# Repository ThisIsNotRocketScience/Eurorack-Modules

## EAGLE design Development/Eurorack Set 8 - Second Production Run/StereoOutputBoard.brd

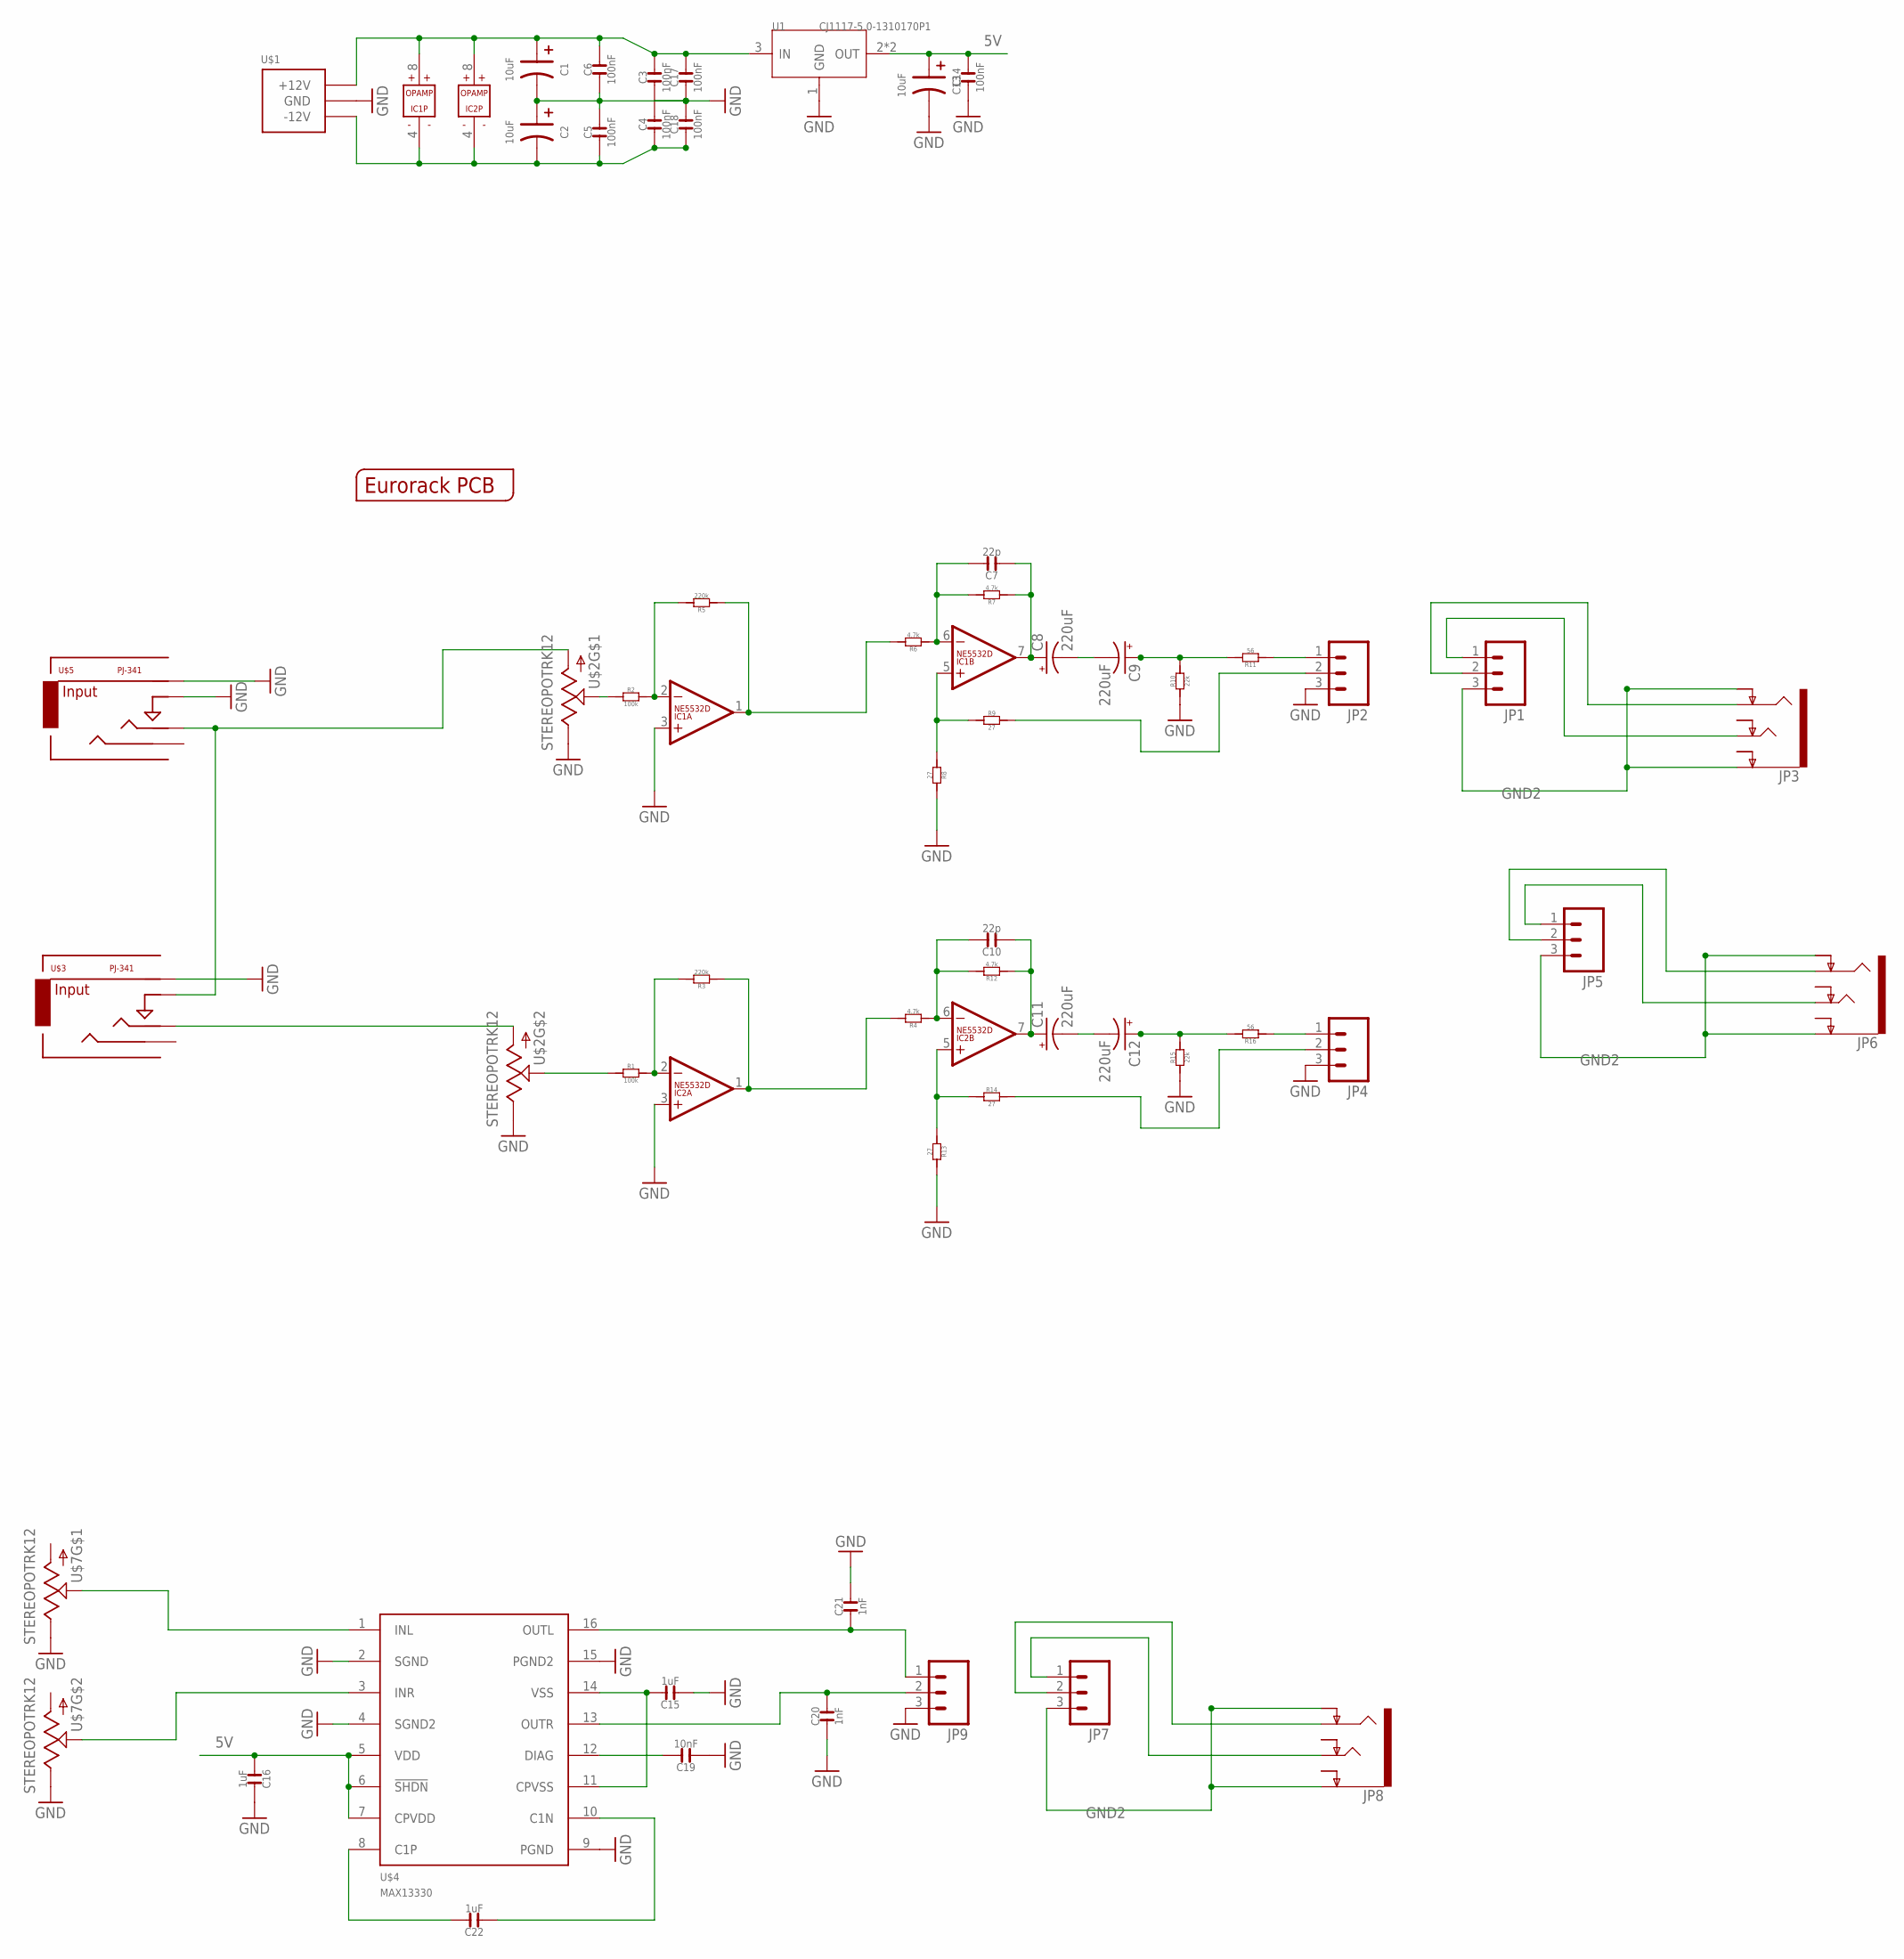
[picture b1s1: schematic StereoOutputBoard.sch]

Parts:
C1, C2, C13: 10uF; AVX-A
C3, C4, C5, C6, C14, C17, C18: 100nF; C0603
C7, C10: 22p; C0603
C8, C9, C11, C12: 220uF; 153CLV-0505
C15, C16, C22: 1uF; C0603
C19: 10nF; C0603
C20, C21: 1nF; C0603
IC1, IC2: NE5532D; SO08
JP1, JP2, JP4, JP5, JP7, JP9: M03PTH; 1X03
JP3, JP6, JP8: AUDIO-JACK4-.25-HORIZ-TRS; AUDIO-JACK-.25-INCH-HORIZ-PTH
R1, R2: 100k; R0603
R3, R5: 220k; R0603
R4, R6, R7, R12: 4.7k; R0603
R8, R9, R13, R14: 27; R0603
R10, R15: 22k; R0603
R11, R16: 56; R0603
U1: CJ1117-5.0-1310170P1; SOT223
U$1: POWER_SIMPLE; 2X05_SMT_HEADER
U$2, U$7: STEREOPOTRK12; RK12
U$3, U$5: PJ-341; 3.5MM-JACK-SWITCH-13MM-INPUT
U$4: MAX13330; QSOP16
U$6: EURORACK_PCB4HP; EURORACK4HPPCB

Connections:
5V: C13.+ (1), C14.2, C16.1, U1.2 (OUT), U1.TER (OUT), U$4.5 (VDD), U$4.6 (!SHDN), U$4.7 (CPVDD)
+12V: C1.+ (1), C3.2, C6.2, C17.2, IC1.8 (V+), IC2.8 (V+), U1.3 (IN), U$1.9 (+12V), U$1.10 (+12V)
-12V: C2.- (2), C4.1, C5.1, C18.1, IC1.4 (V-), IC2.4 (V-), U$1.1 (-12V), U$1.2 (-12V)
GND: C1.- (2), C2.+ (1), C3.1, C4.2, C5.2, C6.1, C13.- (2), C14.1, C15.1, C16.2, C17.1, C18.2, C19.1, C20.1, C21.2, IC1.3 (+IN), IC2.3 (+IN), JP2.3, JP4.3, JP9.3, R8.2, R10.1, R13.2, R15.1, U1.1 (GND), U$1.3 (GND), U$1.4 (GND), U$1.5 (GND), U$1.6 (GND), U$1.7 (GND), U$1.8 (GND), U$2.R1_1 (E), U$2.R2_1 (E), U$3.RING@3 (RING), U$4.2 (SGND), U$4.4 (SGND2), U$4.9 (PGND), U$4.15 (PGND2), U$5.RING@3 (RING), U$5.SWITCH@3 (SWITCH), U$7.R1_1 (E), U$7.R2_1 (E)
GND2: JP1.3, JP3.P$2 (EARTH), JP3.P$5 (RING-NORM), JP5.3, JP6.P$2 (EARTH), JP6.P$5 (RING-NORM), JP7.3, JP8.P$2 (EARTH), JP8.P$5 (RING-NORM)
unnamed: JP2.1, R11.1
unnamed: JP1.1, JP3.P$6 (TIP)
unnamed: C9.+, R10.2, R11.2
unnamed: C7.1, C8.+, IC1.7 (OUT), R7.1
unnamed: IC1.5 (+IN), R8.1, R9.1
unnamed: JP2.2, R9.2
unnamed: C7.2, IC1.6 (-IN), R6.1, R7.2
unnamed: IC1.2 (-IN), R2.2, R5.2
unnamed: JP4.1, R16.1
unnamed: C12.+, R15.2, R16.2
unnamed: C10.1, C11.+, IC2.7 (OUT), R12.1
unnamed: IC1.1 (OUT), R5.1, R6.2
unnamed: C8.-, C9.-
unnamed: R2.1, U$2.R1_2 (S)
unnamed: IC2.5 (+IN), R13.1, R14.1
unnamed: JP4.2, R14.2
unnamed: C10.2, IC2.6 (-IN), R4.1, R12.2
unnamed: JP1.2, JP3.P$4 (RING)
unnamed: IC2.2 (-IN), R1.2, R3.2
unnamed: R1.1, U$2.R2_2 (S)
unnamed: IC2.1 (OUT), R3.1, R4.2
unnamed: C11.-, C12.-
unnamed: U$2.R1_3 (A), U$3.SWITCH@3 (SWITCH), U$5.TIP@3 (TIP)
unnamed: U$2.R2_3 (A), U$3.TIP@3 (TIP)
unnamed: JP5.1, JP6.P$6 (TIP)
unnamed: JP5.2, JP6.P$4 (RING)
unnamed: JP7.1, JP8.P$6 (TIP)
unnamed: JP7.2, JP8.P$4 (RING)
unnamed: C15.2, U$4.11 (CPVSS), U$4.14 (VSS)
unnamed: C19.2, U$4.12 (DIAG)
unnamed: C21.1, JP9.1, U$4.16 (OUTL)
unnamed: C20.2, JP9.2, U$4.13 (OUTR)
unnamed: C22.2, U$4.8 (C1P)
unnamed: C22.1, U$4.10 (C1N)
unnamed: U$4.1 (INL), U$7.R1_2 (S)
unnamed: U$4.3 (INR), U$7.R2_2 (S)

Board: 2 copper layers, 57 parts (1 on the bottom side), 41 nets, no tracks yet.

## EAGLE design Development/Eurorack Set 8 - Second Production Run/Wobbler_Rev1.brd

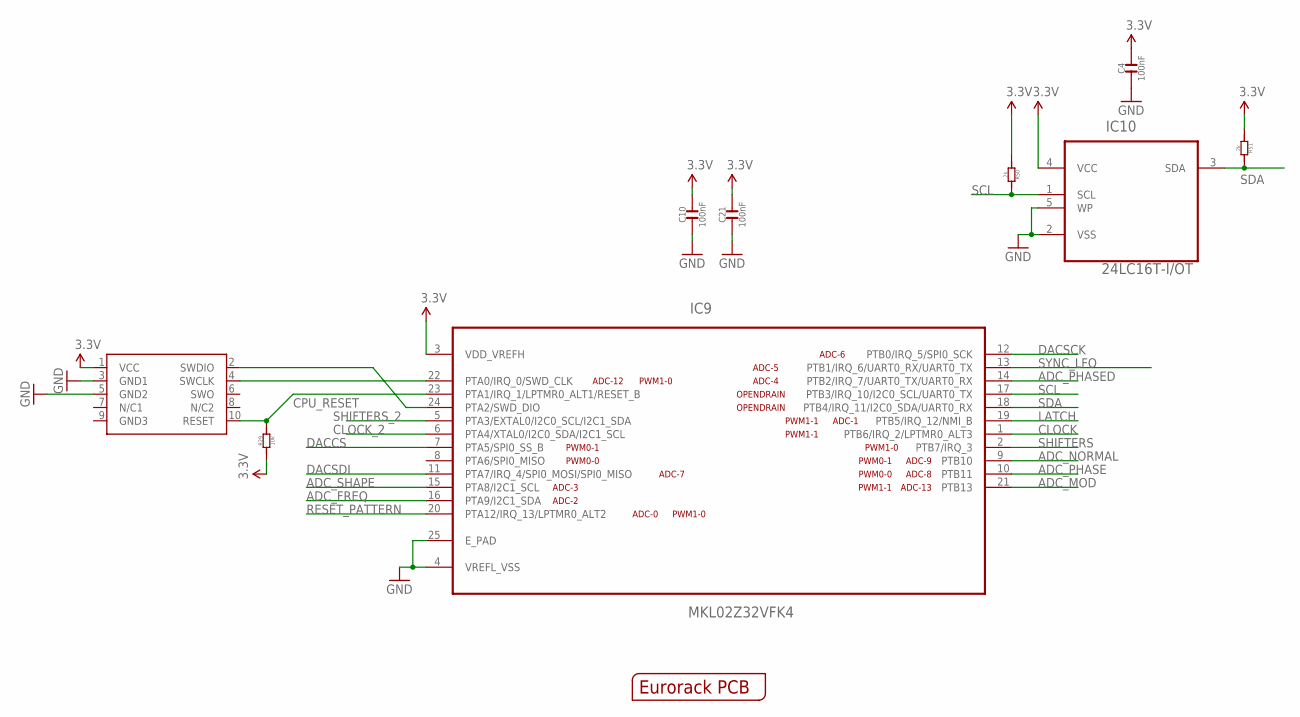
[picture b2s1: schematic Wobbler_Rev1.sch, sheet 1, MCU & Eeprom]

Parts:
C4, C10, C21: 100nF; C0603; MPN MC0603F104Z160CT
IC9: MKL02Z32VFK4; QFN50P400X400X100-25N
IC10: 24LC16T-I/OT; SOT95P290X145-5N; MPN 24LC00T-I/OT
OUTLINE: EURORACK_PCB12HP; EURORACK12HPPCB
R29: 10k; R0603
R50, R51: 2k; R0603
SWD1: CORTEX_SWD; M50-3600542

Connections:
3.3V: C4.2, C10.2, C21.2, IC9.3 (VDD_VREFH), IC10.4 (VCC), R29.1, R50.1, R51.1, SWD1.1 (VCC); also elsewhere on the board
ADC_FREQ: IC9.16 (PTA9/I2C1_SDA); also elsewhere on the board
ADC_MOD: IC9.21 (PTB13); also elsewhere on the board
ADC_NORMAL: IC9.9 (PTB10); also elsewhere on the board
ADC_PHASE: IC9.10 (PTB11); also elsewhere on the board
ADC_PHASED: IC9.14 (PTB2/IRQ_7/UART0_TX/UART0_RX); also elsewhere on the board
ADC_SHAPE: IC9.15 (PTA8/I2C1_SCL); also elsewhere on the board
CLOCK: IC9.1 (PTB6/IRQ_2/LPTMR0_ALT3); also elsewhere on the board
CLOCK_2: IC9.6 (PTA4/XTAL0/I2C0_SDA/I2C1_SCL); also elsewhere on the board
CPU_RESET: IC9.23 (PTA1/IRQ_1/LPTMR0_ALT1/RESET_B), R29.2, SWD1.10 (RESET)
DACCS: IC9.7 (PTA5/SPI0_SS_B); also elsewhere on the board
DACSCK: IC9.12 (PTB0/IRQ_5/SPI0_SCK); also elsewhere on the board
DACSDI: IC9.11 (PTA7/IRQ_4/SPI0_MOSI/SPI0_MISO); also elsewhere on the board
GND: C4.1, C10.1, C21.1, IC9.4 (VREFL_VSS), IC9.25 (E_PAD), IC10.2 (VSS), IC10.5 (WP), SWD1.3 (GND1), SWD1.5 (GND2); also elsewhere on the board
LATCH: IC9.19 (PTB5/IRQ_12/NMI_B); also elsewhere on the board
RESET_PATTERN: IC9.20 (PTA12/IRQ_13/LPTMR0_ALT2); also elsewhere on the board
SCL: IC9.17 (PTB3/IRQ_10/I2C0_SCL/UART0_TX), IC10.1 (SCL), R50.2
SDA: IC9.18 (PTB4/IRQ_11/I2C0_SDA/UART0_RX), IC10.3 (SDA), R51.2
SHIFTERS: IC9.2 (PTB7/IRQ_3); also elsewhere on the board
SHIFTERS_2: IC9.5 (PTA3/EXTAL0/I2C0_SCL/I2C1_SDA); also elsewhere on the board
SWD_CLK: IC9.22 (PTA0/IRQ_0/SWD_CLK), SWD1.4 (SWCLK)
SWD_DIO: IC9.24 (PTA2/SWD_DIO), SWD1.2 (SWDIO)
SYNC_LFO: IC9.13 (PTB1/IRQ_6/UART0_RX/UART0_TX); also elsewhere on the board

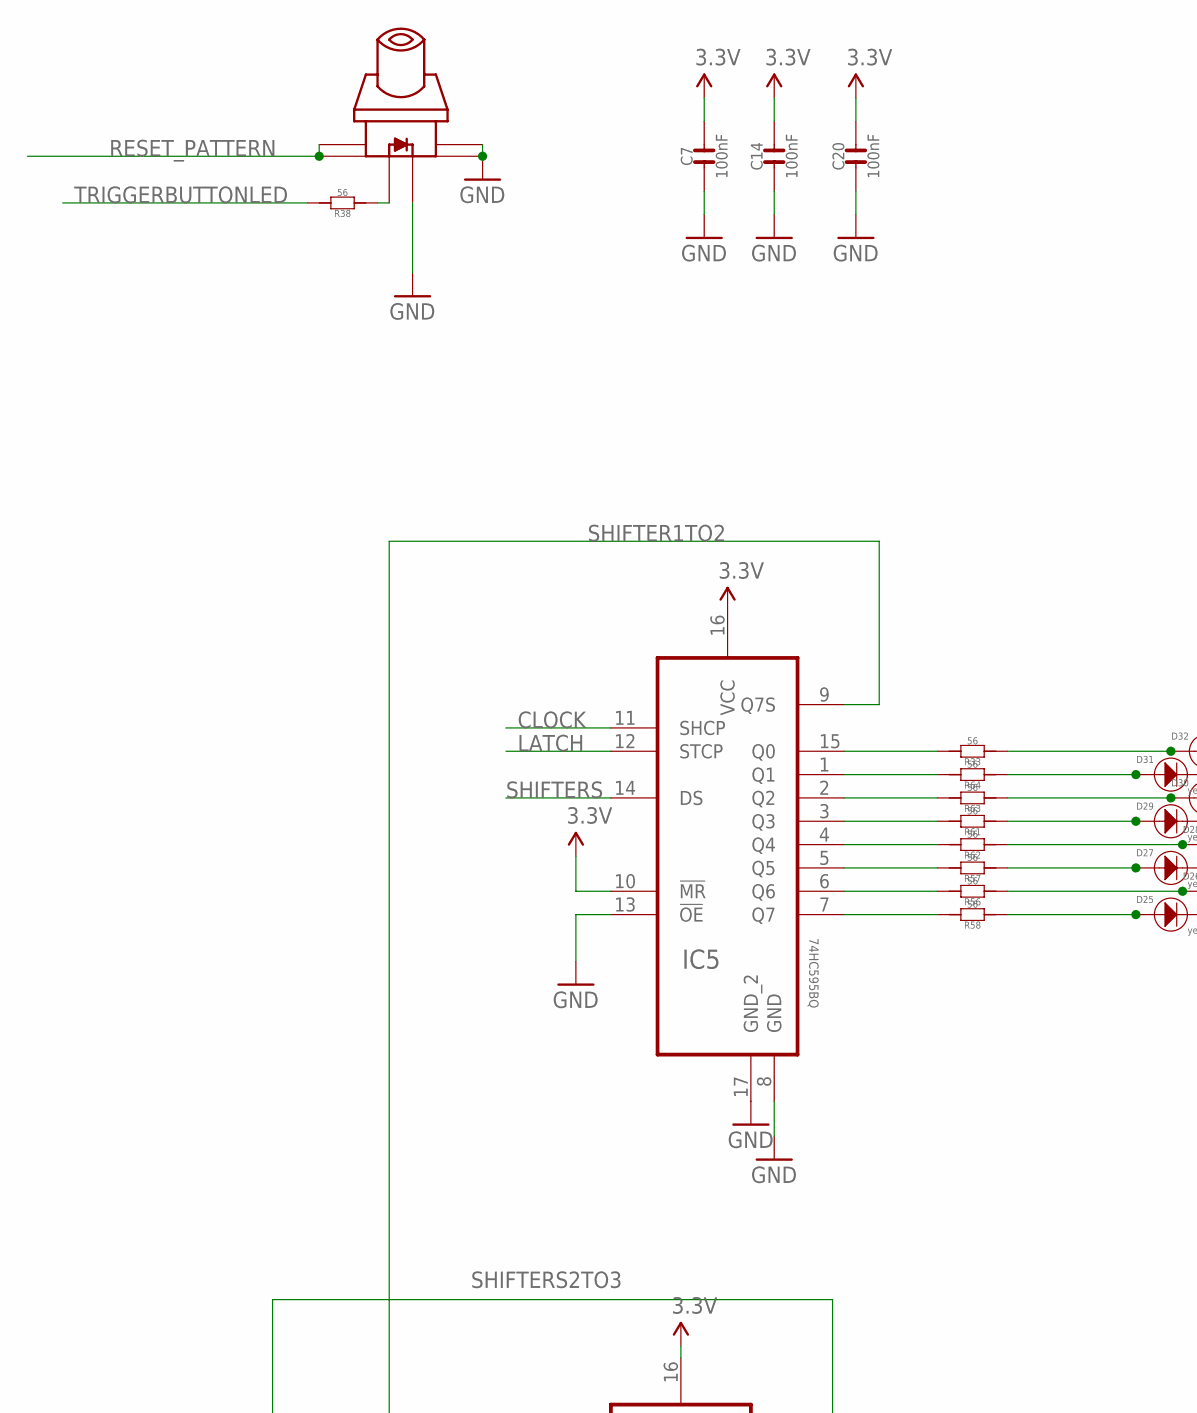
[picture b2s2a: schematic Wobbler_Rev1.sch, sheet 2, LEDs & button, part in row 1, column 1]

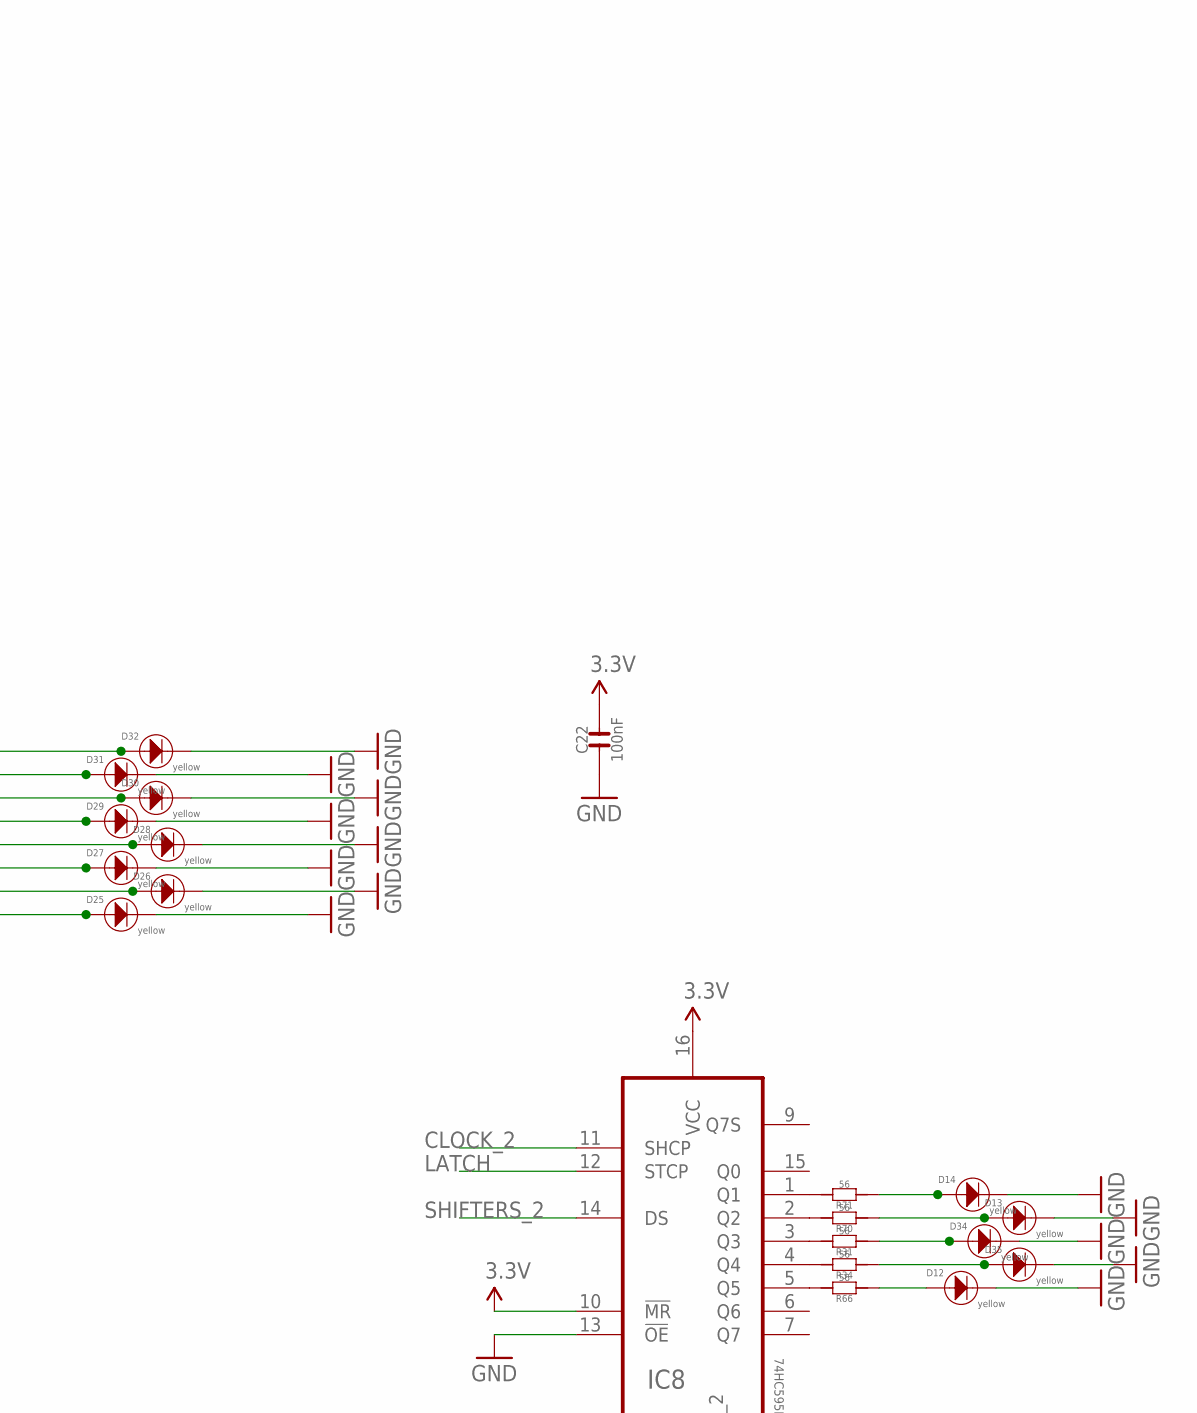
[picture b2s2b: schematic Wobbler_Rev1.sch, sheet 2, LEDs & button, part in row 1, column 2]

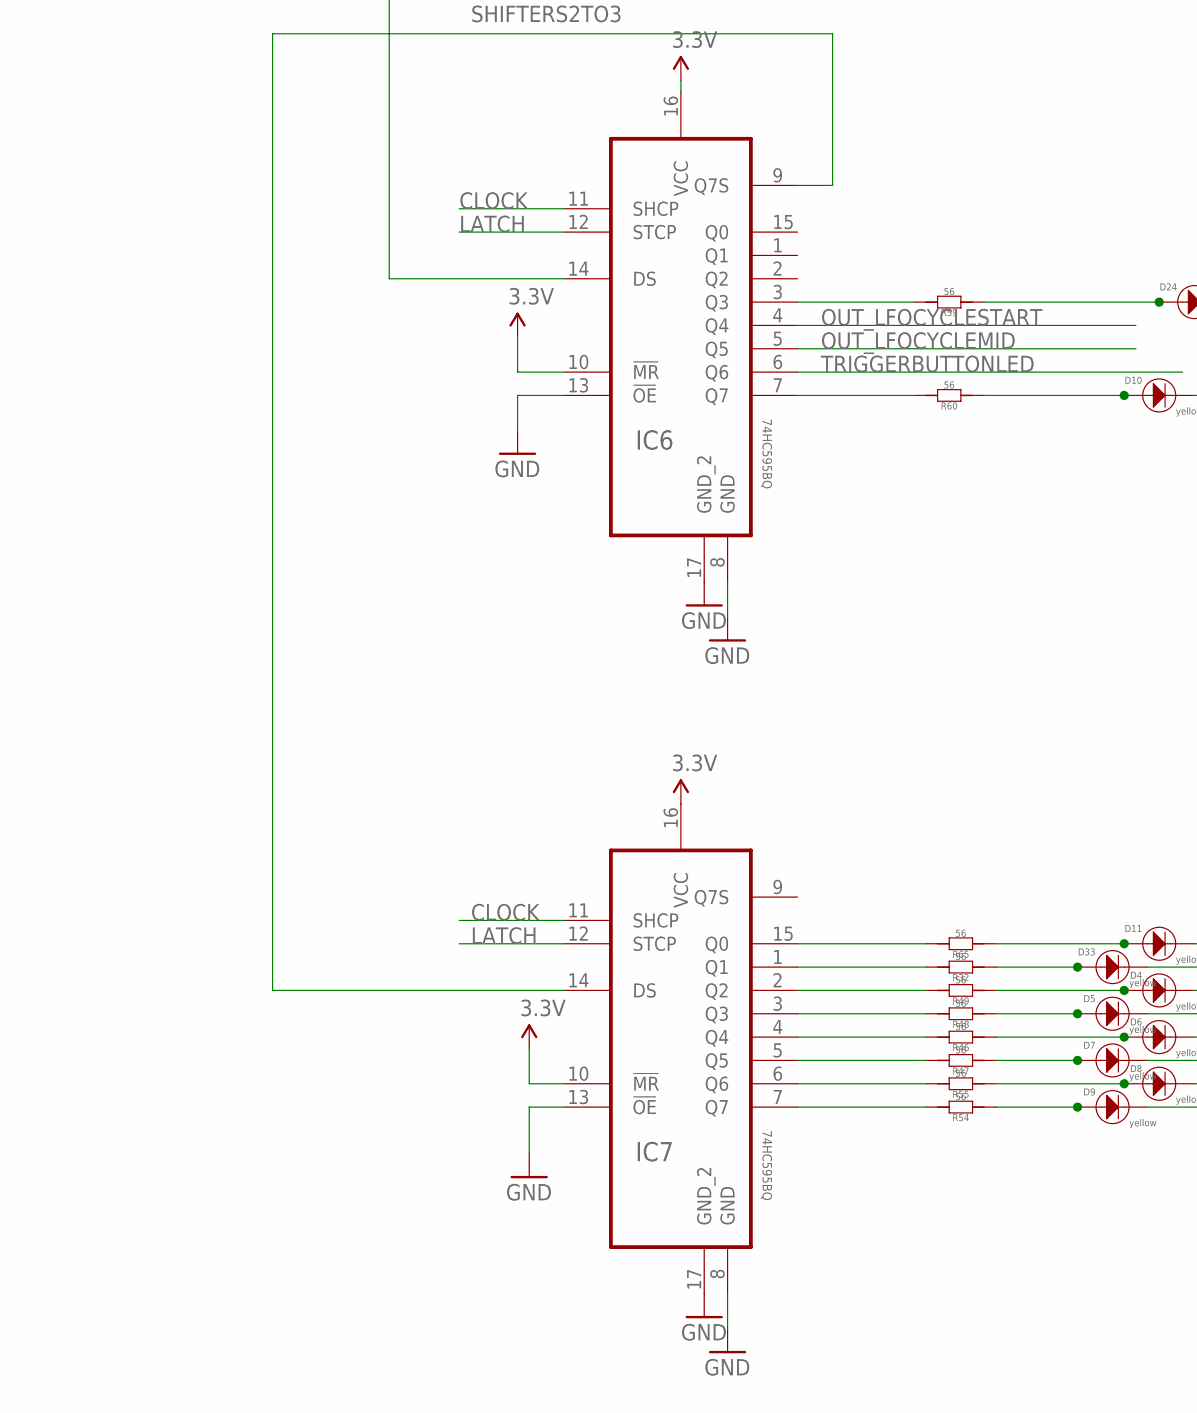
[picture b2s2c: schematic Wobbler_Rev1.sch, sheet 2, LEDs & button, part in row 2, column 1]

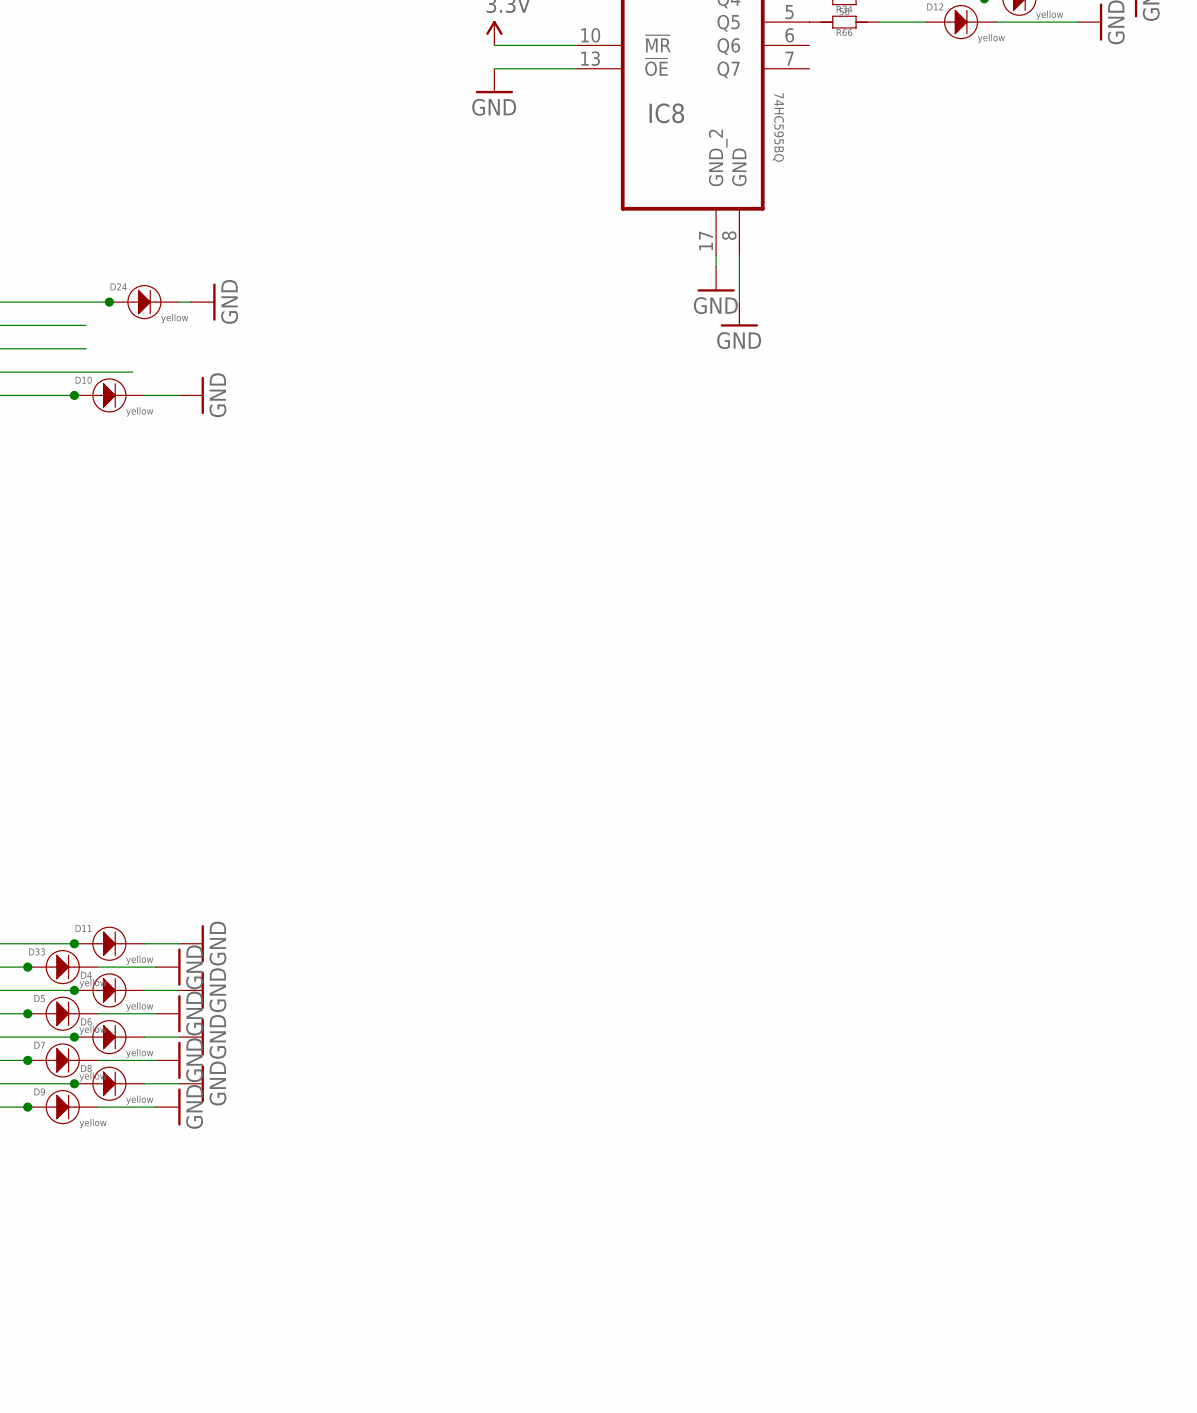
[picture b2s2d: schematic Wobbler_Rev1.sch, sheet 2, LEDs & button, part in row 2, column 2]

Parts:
C7, C14, C20, C22: 100nF; C0603; MPN MC0603F104Z160CT
D4, D5, D6, D7, D8, D9, D10, D11, D12, D13, D14, D24, D25, D26, D27, D28, D29, D30, D31, D32, D33, D34, D35: yellow; 3MMLED
IC5, IC6, IC7, IC8: 74HC595BQ; QFN50P250X350X100-17N
R31, R32, R33, R34, R38, R46, R47, R48, R49, R54, R55, R56, R57, R58, R59, R60, R61, R62, R63, R64, R65, R66, R70, R71: 56; R0603
U$1: SWITCH_W_LED_PB6149L-X-102YELLOW; PB6149L

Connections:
3.3V: C7.2, C14.2, C20.2, C22.2, IC5.10 (!MR), IC5.16 (VCC), IC6.10 (!MR), IC6.16 (VCC), IC7.10 (!MR), IC7.16 (VCC), IC8.10 (!MR), IC8.16 (VCC); also elsewhere on the board
CLOCK: IC5.11 (SHCP), IC6.11 (SHCP), IC7.11 (SHCP); also elsewhere on the board
CLOCK_2: IC8.11 (SHCP); also elsewhere on the board
GND: C7.1, C14.1, C20.1, C22.1, D4.-, D5.-, D6.-, D7.-, D8.-, D9.-, D10.-, D11.-, D12.-, D13.-, D14.-, D24.-, D25.-, D26.-, D27.-, D28.-, D29.-, D30.-, D31.-, D32.-, D33.-, D34.-, D35.-, IC5.8 (GND), IC5.13 (!OE), IC5.17 (GND_2), IC6.8 (GND), IC6.13 (!OE), IC6.17 (GND_2), IC7.8 (GND), IC7.13 (!OE), IC7.17 (GND_2), IC8.8 (GND), IC8.13 (!OE), IC8.17 (GND_2), U$1.3, U$1.4, U$1.LEDNEG (NEG); also elsewhere on the board
LATCH: IC5.12 (STCP), IC6.12 (STCP), IC7.12 (STCP), IC8.12 (STCP); also elsewhere on the board
unnamed: IC5.15 (Q0), R33.2
unnamed: D7.+, R47.1
unnamed: IC5.1 (Q1), R64.2
unnamed: IC5.2 (Q2), R63.2
unnamed: IC5.3 (Q3), R61.2
unnamed: D28.+, R62.1
unnamed: IC5.4 (Q4), R62.2
unnamed: IC5.5 (Q5), R57.2
unnamed: D29.+, R61.1
unnamed: IC5.6 (Q6), R56.2
unnamed: IC5.7 (Q7), R58.2
unnamed: IC6.3 (Q3), R59.2
unnamed: IC7.7 (Q7), R54.2
unnamed: IC7.6 (Q6), R55.2
unnamed: IC7.5 (Q5), R47.2
unnamed: R38.1, U$1.LEDPOS (POS)
unnamed: D13.+, R70.1
unnamed: IC7.4 (Q4), R46.2
unnamed: D6.+, R46.1
unnamed: D5.+, R48.1
unnamed: D4.+, R49.1
unnamed: D8.+, R55.1
unnamed: D9.+, R54.1
unnamed: D10.+, R60.1
unnamed: D11.+, R65.1
unnamed: IC7.3 (Q3), R48.2
unnamed: IC7.2 (Q2), R49.2
unnamed: IC7.1 (Q1), R32.2
unnamed: IC7.15 (Q0), R65.2
unnamed: IC6.7 (Q7), R60.2
unnamed: D14.+, R71.1
unnamed: IC8.1 (Q1), R71.2
unnamed: IC8.2 (Q2), R70.2
unnamed: D12.+, R66.1
unnamed: IC8.3 (Q3), R31.2
unnamed: IC8.4 (Q4), R34.2
unnamed: IC8.5 (Q5), R66.2
unnamed: D27.+, R57.1
unnamed: D26.+, R56.1
unnamed: D25.+, R58.1
unnamed: D24.+, R59.1
unnamed: D30.+, R63.1
unnamed: D31.+, R64.1
unnamed: D32.+, R33.1
unnamed: D33.+, R32.1
unnamed: D34.+, R31.1
unnamed: D35.+, R34.1
OUT_LFOCYCLEMID: IC6.5 (Q5); also elsewhere on the board
OUT_LFOCYCLESTART: IC6.4 (Q4); also elsewhere on the board
RESET_PATTERN: U$1.1, U$1.2; also elsewhere on the board
SHIFTER1TO2: IC5.9 (Q7S), IC6.14 (DS)
SHIFTERS: IC5.14 (DS); also elsewhere on the board
SHIFTERS2TO3: IC6.9 (Q7S), IC7.14 (DS)
SHIFTERS_2: IC8.14 (DS); also elsewhere on the board
TRIGGERBUTTONLED: IC6.6 (Q6), R38.2

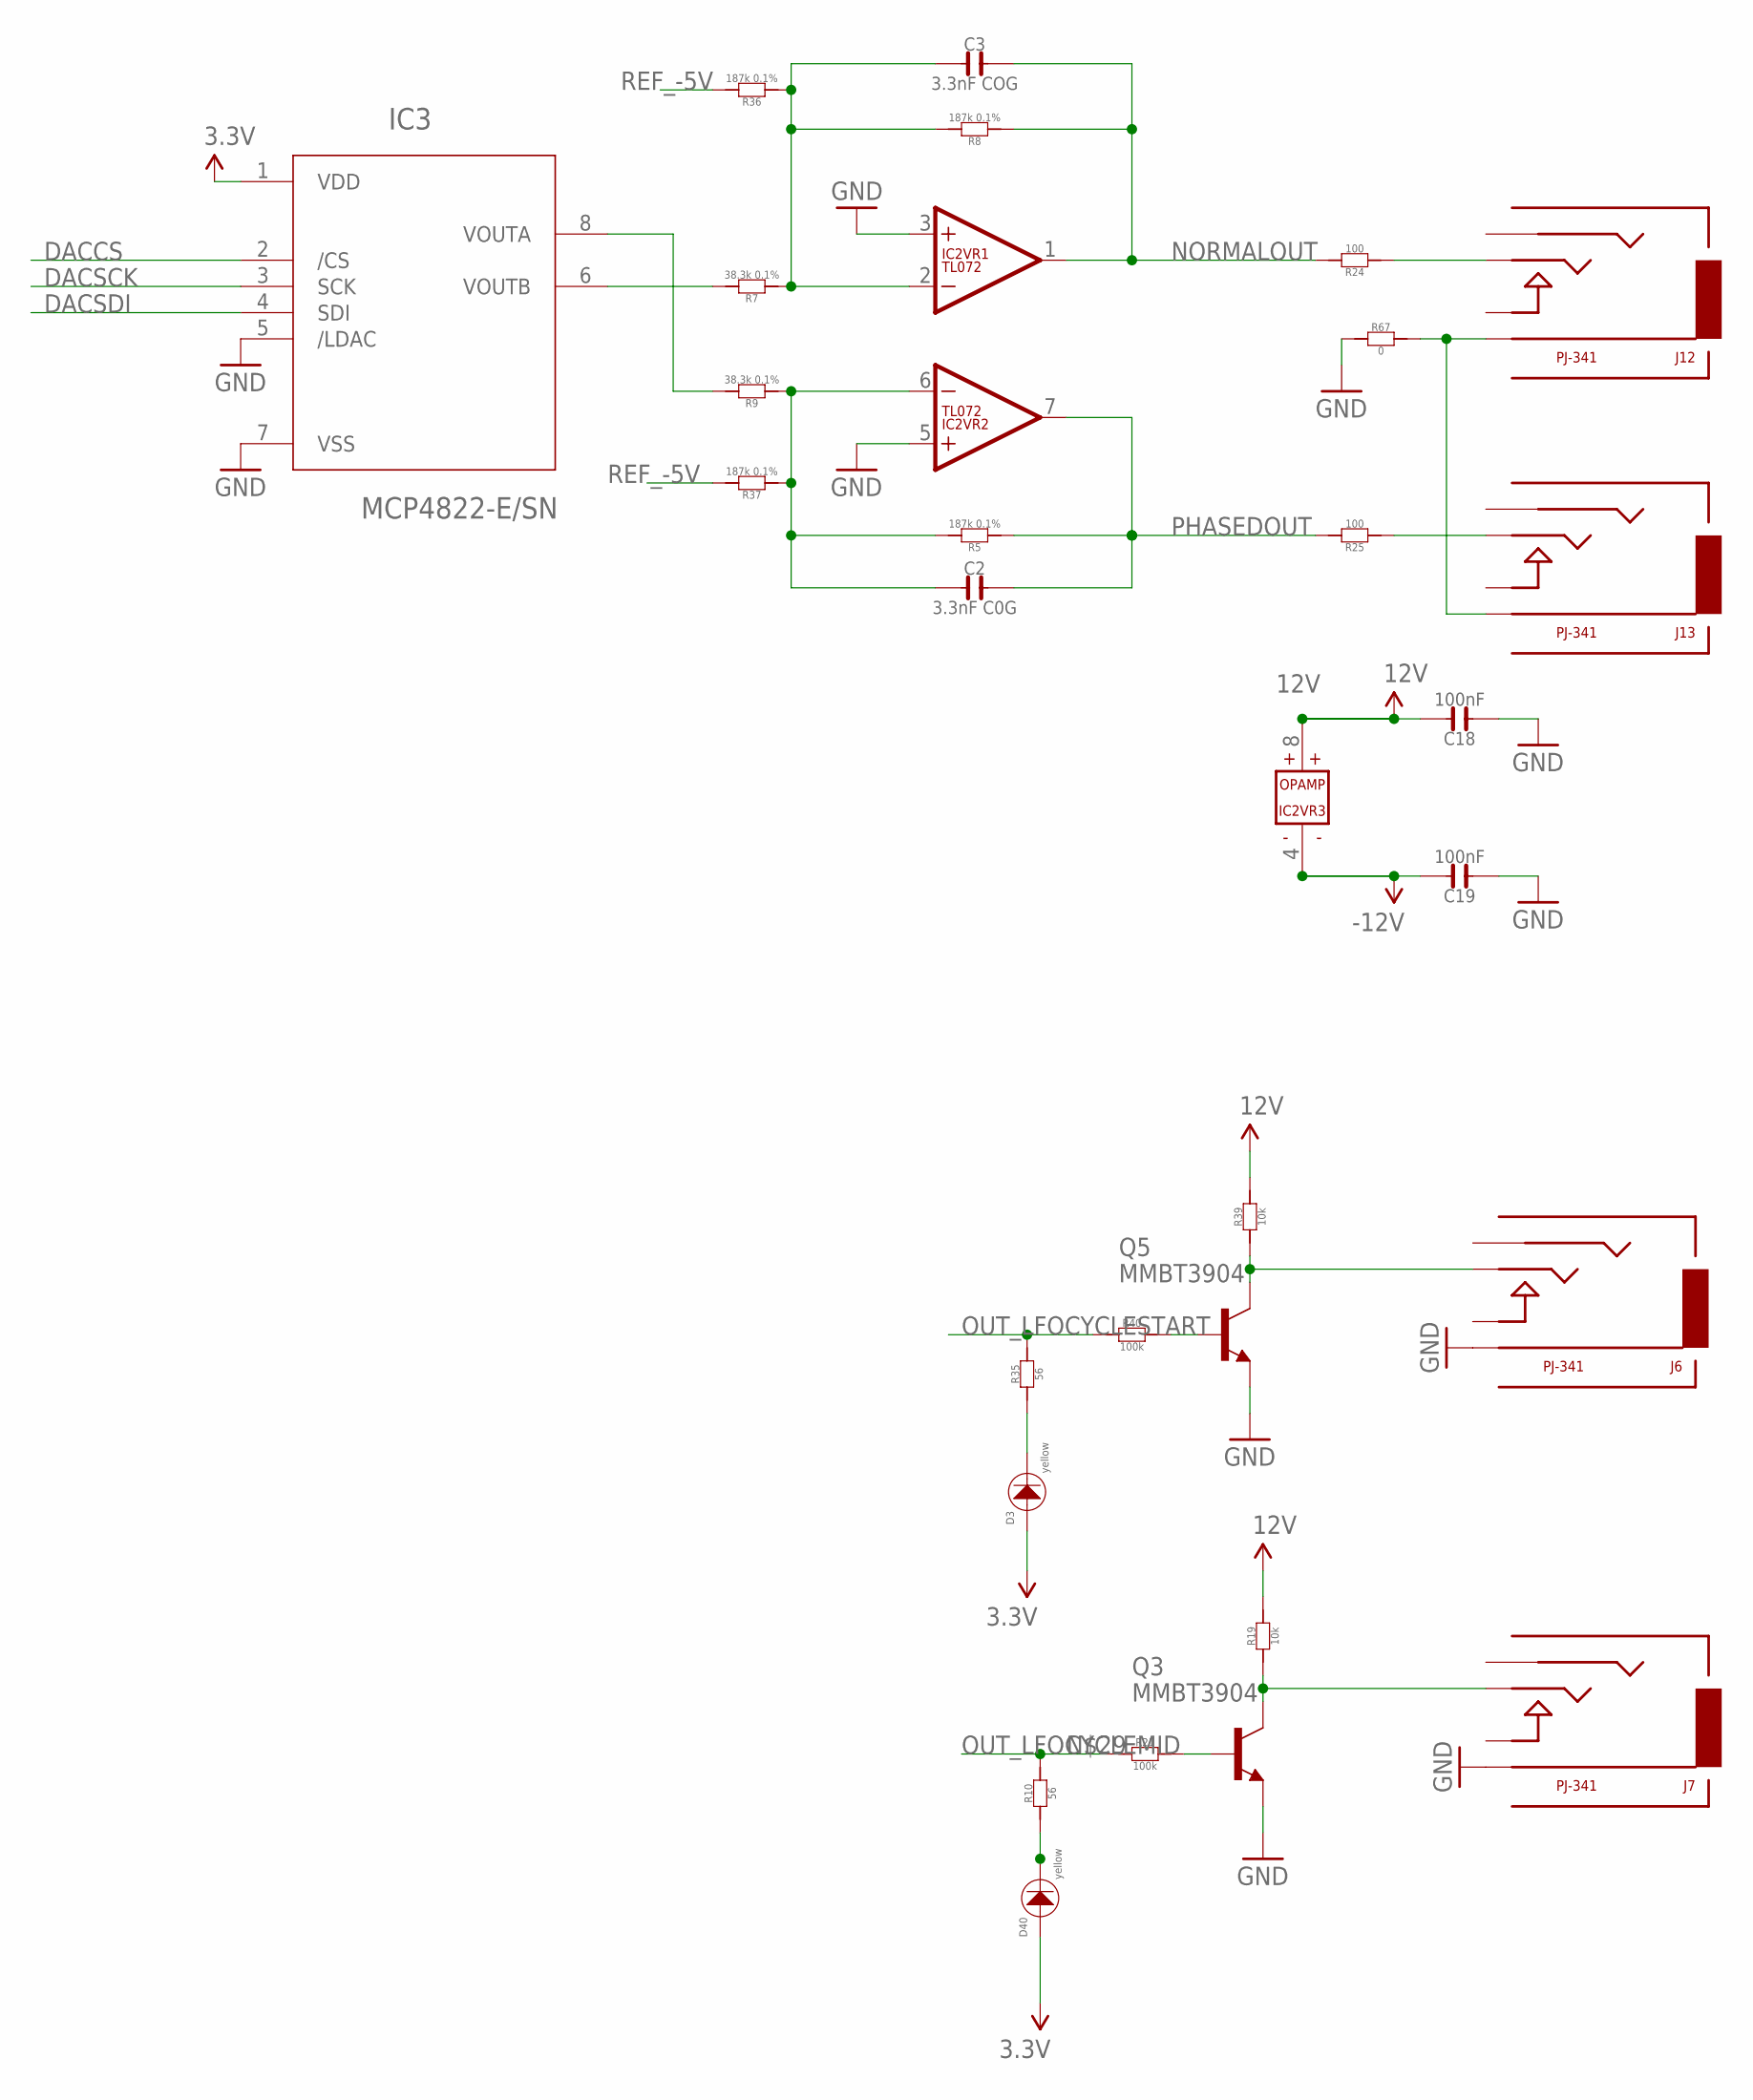
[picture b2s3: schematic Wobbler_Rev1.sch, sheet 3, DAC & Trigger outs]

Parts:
C2: 3.3nF C0G; C0603
C3: 3.3nF COG; C0603
C18, C19: 100nF; C0603; MPN MC0603F104Z160CT
D3, D40: yellow; 3MMLED
IC2: TL072; SO08
IC3: MCP4822-E/SN; SOIC8-N_MC
J6, J7, J12, J13: PJ-341; 3.5MM-JACK-SWITCH-13MM-OUTPUT
Q3, Q5: MMBT3904; SOT23-BEC; MPN PMBT3904,215
R5, R8, R36, R37: 187k 0.1%; R0603
R7, R9: 38.3k 0.1%; R0603
R10, R35: 56; R0603
R19, R39: 10k; R0603
R21, R40: 100k; R0603
R24, R25: 100; R0603
R67: 0; R0603

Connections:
3.3V: D3.+, D40.+, IC3.1 (VDD); also elsewhere on the board
12V: C18.2, IC2.8 (V+), R19.2, R39.2; also elsewhere on the board
-12V: C19.2, IC2.4 (V-); also elsewhere on the board
DACCS: IC3.2 (/CS); also elsewhere on the board
DACSCK: IC3.3 (SCK); also elsewhere on the board
DACSDI: IC3.4 (SDI); also elsewhere on the board
GND: C18.1, C19.1, IC2.3 (+IN), IC2.5 (+IN), IC3.5 (/LDAC), IC3.7 (VSS), J6.RING@3 (RING), J7.RING@3 (RING), Q3.E, Q5.E, R67.1; also elsewhere on the board
unnamed: IC3.8 (VOUTA), R9.2
unnamed: IC3.6 (VOUTB), R7.2
unnamed: C2.1, IC2.6 (-IN), R5.2, R9.1, R37.1
unnamed: C3.1, IC2.2 (-IN), R7.1, R8.2, R36.1
unnamed: J13.TIP@3 (TIP), R25.1
unnamed: J12.TIP@3 (TIP), R24.1
unnamed: D40.-, R10.1
unnamed: Q3.B, R21.2
unnamed: D3.-, R35.1
unnamed: J7.TIP@3 (TIP), Q3.C, R19.1
unnamed: Q5.B, R40.2
unnamed: J6.TIP@3 (TIP), Q5.C, R39.1
NORMALOUT: C3.2, IC2.1 (OUT), R8.1, R24.2
OUT_LFOCYCLEMID: R10.2, R21.1; also elsewhere on the board
OUT_LFOCYCLESTART: R35.2, R40.1; also elsewhere on the board
PHASEDOUT: C2.2, IC2.7 (OUT), R5.1, R25.2
REF_-5V: R36.2, R37.2; also elsewhere on the board
RETURNGROUND: J12.RING@3 (RING), J13.RING@3 (RING), R67.2

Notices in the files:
parts and their libraries:
SparkFun-Connectors: Licensing: CC v3.0 Share-Alike You are welcome to use this library for commercial purposes.
